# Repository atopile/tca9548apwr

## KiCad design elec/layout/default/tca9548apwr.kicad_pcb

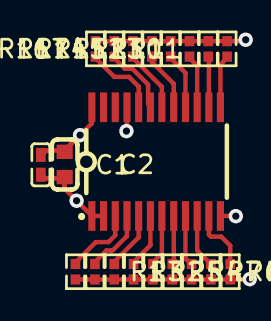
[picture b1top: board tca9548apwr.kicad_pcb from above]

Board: 2 copper layers, 20 parts (0 on the bottom side), 19 nets.

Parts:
C1: 100nF ±10% 16V X7R; C0402-b3ef17
C2: 2.2µF ±10% 16V X5R; C0603-bd72f6
R1, R2, R3, R4, R5, R6, R7, R8, R9, R10, R11, R12, R13, R14, R15, R16, R17: 10kΩ ±1% 62.5mW; R0402-56259e
U1: TSSOP-24_L7.8-W4.4-P0.65-LS6.4-BL

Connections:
gnd: C1.2, C2.2, U1.1, U1.2, U1.12, U1.21
hv: C1.1, C2.1, R1.2, R2.2, R3.2, R4.2, R5.2, R6.2, R7.2, R8.2, R9.2, R10.2, R11.2, R12.2, R13.2, R14.2, R15.2, R16.2, R17.2, U1.24
line: R12.1, U1.16
line-1: R5.1, U1.6
line-2: R14.1, U1.18
line-3: R15.1, U1.17
line-4: R3.1, U1.4
line-5: R16.1, U1.20
line-6: R9.1, U1.10
line-7: R7.1, U1.8
line-8: R11.1, U1.13
line-9: R6.1, U1.9
line-10: R10.1, U1.14
line-11: R8.1, U1.11
line-12: R4.1, U1.7
line-13: R1.1, U1.3
line-14: R2.1, U1.5
line-15: R17.1, U1.19
line-16: R13.1, U1.15

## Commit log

2024-02-13 Configure project
2024-02-15 layout
2024-05-09 Add pullup to reset line
2024-05-09 Remove other projects .kicad_pro files
2024-05-09 Add reset resistor to layout
2024-10-16 Remove xmas characters from layout
2025-01-10 run build, update layout
2025-03-07 update syntax and link layout
2025-03-07 remove generics dep
2025-03-07 Update ci.yml
    update github action upload version
    use main to build
2025-03-07 Fix frozen
2025-03-31 update to kicad 9 and fix resistor orientation
2025-04-05 build with latest
